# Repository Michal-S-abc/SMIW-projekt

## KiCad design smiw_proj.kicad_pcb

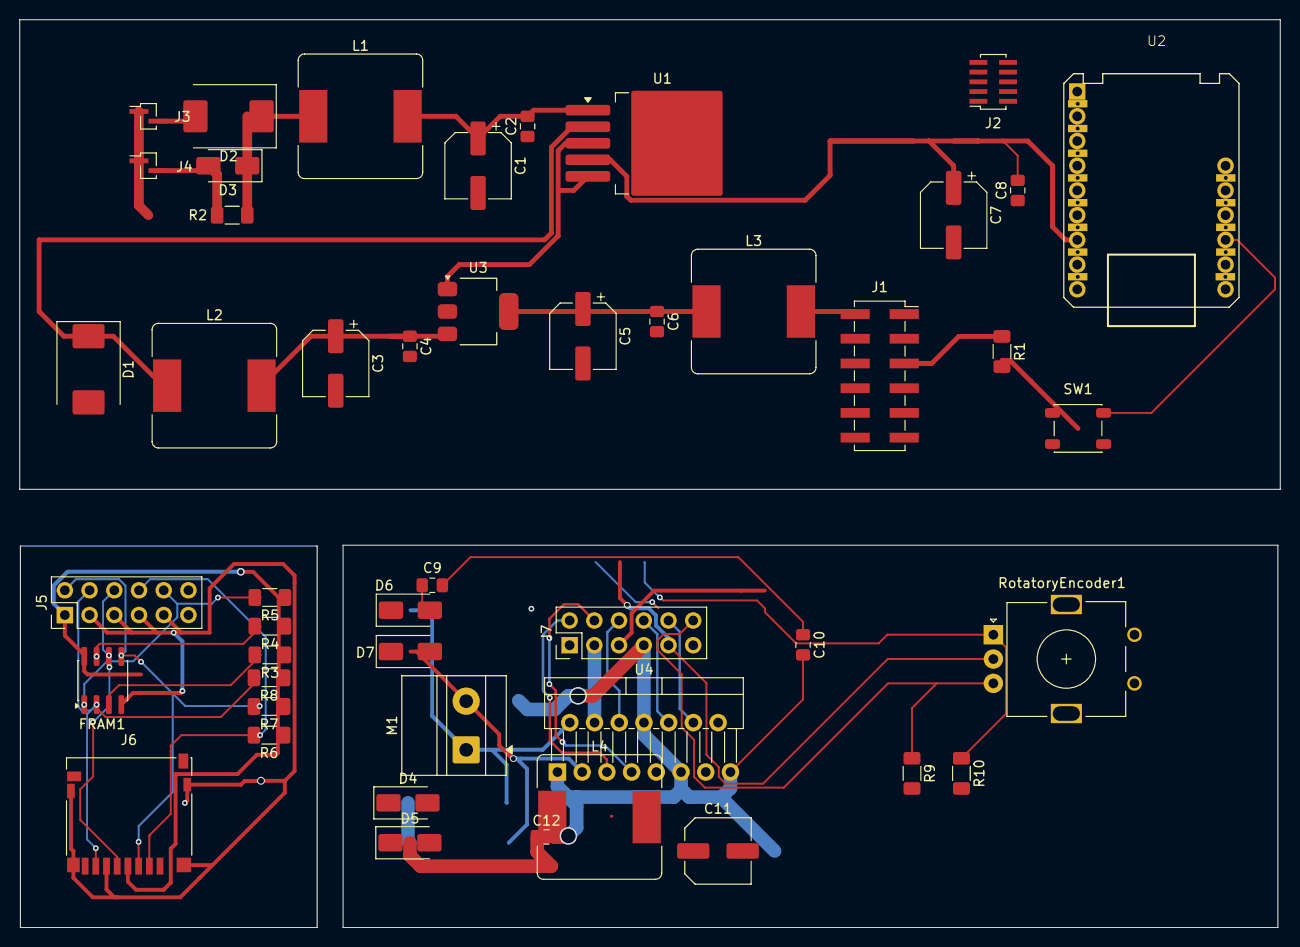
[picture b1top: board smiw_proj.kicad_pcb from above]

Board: 2 copper layers, 129.5 x 93.3 mm, 48 parts (0 on the bottom side), 31 nets.

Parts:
C1, C7: 100uF/16V; CP_Elec_6.3x5.3
C2, C6, C8, C9, C10, C12: 100nF; C_0805_2012Metric_Pad1.18x1.45mm_HandSolder
C3: 220uF/6V3; CP_Elec_6.3x5.3
C4: 220nF; C_0805_2012Metric_Pad1.18x1.45mm_HandSolder
C5: 10uF/16V; CP_Elec_6.3x5.3
C11: 100uF/16V; C_Elec_6.3x7.7
D1: 1N5824; D_SMC
D2: SS14; D_SMC
D3: SS14; D_SMA
D4, D5, D6, D7: 1N4001; D_SMA
FRAM1: CY15B104Q; SOIC-8_3.9x4.9mm_P1.27mm
J1: Conn_02x06_Odd_Even; PinSocket_2x06_P2.54mm_Vertical_SMD
J2: Conn_02x05_Odd_Even; PinSocket_2x05_P1.00mm_Vertical_SMD
J3, J4: Conn_01x02; PinSocket_1x02_P1.00mm_Vertical_SMD_Pin1Left
J5: Conn_02x05_Odd_Even; PinHeader_2x06_P2.54mm_Vertical
J6: Molex 104031; microSD_HC_Hirose_DM3D-SF
J7: Conn_02x06_Odd_Even; PinHeader_2x06_P2.54mm_Vertical
L1, L3: 10uH; L_Bourns_SRR1260
L2: 33uH; L_Bourns_SRR1260
L4: 1uH; L_Bourns_SRR1260
M1: JGB37-520; TerminalBlock_MetzConnect_Type011_RT05502HBLC_1x02_P5.00mm_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
R1, R3, R4, R5, R6, R7, R8: 10k; R_1206_3216Metric_Pad1.30x1.75mm_HandSolder
R2, R9, R10: 1k; R_1206_3216Metric_Pad1.30x1.75mm_HandSolder
RotatoryEncoder1: EC11E15204A3; RotaryEncoder_Alps_EC11E_Vertical_H20mm
SW1: SW_Push; SW_SPST_PTS647_Sx50
U1: LM2596S-5; TO-263-5_TabPin3
U2: M5 Stamp-S3; M5Stamp-S3
U3: LD1117S33TR_SOT223; SOT-223-3_TabPin2
U4: L298N; TO-220-15_P2.54x5.08mm_StaggerOdd_Lead4.58mm_Vertical

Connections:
12V: D2.1 (K), D3.1 (K), J1.1, J7.1, L1.1, L4.1, R2.1
/DRIVER IN1: J1.2, J7.2, U2.1 (g1), U4.5 (IN1)
/DRIVER IN2: J1.4, J7.4, U2.2 (g2), U4.7 (IN2)
/DRIVER IN3: J1.8, J7.8, U2.3 (g3), U4.10 (IN3)
/DRIVER IN4: J1.10, J7.10, U2.9 (g9), U4.12 (IN4)
/ENC A: J1.11, J7.11, R10.1, RotatoryEncoder1.A, U2.10 (g10)
/ENC B: J1.12, J7.12, R9.1, RotatoryEncoder1.B, U2.12 (g11)
/MISO: FRAM1.2 (SO), J2.4, J5.4, J6.7 (DAT0), R8.2, U2.4 (g4)
/MOSI: FRAM1.5 (SI), J2.2, J5.2, J6.3 (CMD), R7.2, U2.5 (g5)
/PWM A: J1.6, J7.6, U2.14 (g12), U4.6 (EnA)
/SCK: FRAM1.6 (SCK), J2.6, J5.6, J6.5 (CLK), U2.6 (g6)
/reset: R1.2, SW1.1, U2.22 (en)
//FRAM CS: FRAM1.1 (~CS), J5.10, R5.2
//SD CS: J5.8, J6.2 (DAT3/CD), R6.2
/~FRAM CS: J2.10, U2.8 (g8)
/~SD CS: J2.8, U2.7 (g7)
CPU_GND: J1.9, J7.9, RotatoryEncoder1.C
GND: C1.2, C2.1, C3.2, C4.2, C5.2, C6.2, C7.2, C8.1, C9.1, C10.2, C11.2, C12.2, D1.2 (A), D6.2 (A), D7.2 (A), FRAM1.4 (V_{SS}), J1.7, J2.3, J2.5, J2.7, J2.9, J3.1, J4.1, J5.3, J5.5, J5.7, J5.9, J6.6 (VSS), J6.SH (SHIELD), J7.7, SW1.2, U1.3 (GND), U1.5 (~ON/OFF), U2.11 (gnd), U2.18 (gnd), U3.1 (GND), U4.1 (SENSE_A), U4.8 (GND), U4.11 (EnB), U4.15 (SENSE_B)
unnamed: D1.1 (K), L2.1, U1.2 (OUT)
unnamed: D2.2 (A), J3.2
unnamed: D3.2 (A), J4.2, R2.2
unnamed: D4.2 (A), D6.1 (K), M1.1 (+), U4.2 (OUT1)
unnamed: C11.1, C12.1, D4.1 (K), D5.1 (K), L4.2, U4.9 (Vss)
unnamed: D5.2 (A), D7.1 (K), M1.2 (-), U4.3 (OUT2)
unnamed: FRAM1.7 (~HOLD), R4.2
unnamed: FRAM1.3 (~WP), R3.2
unnamed: C1.1, C2.2, L1.2, U1.1 (VIN)
unnamed: C5.1, C6.1, L3.1, U3.2 (VO)
VDD: C9.2, C10.1, FRAM1.8 (V_{CC}), J5.1, J6.4 (VDD), R3.1, R4.1, R5.1, R6.1, R7.1, R8.1
Vcc: C3.1, C4.1, C7.1, C8.2, J1.3, J7.3, L2.2, U1.4 (FB), U2.13 (5V), U3.3 (VI), U4.4 (Vs)
Vdd: J1.5, J2.1, J7.5, L3.2, R1.1, R9.2, R10.2

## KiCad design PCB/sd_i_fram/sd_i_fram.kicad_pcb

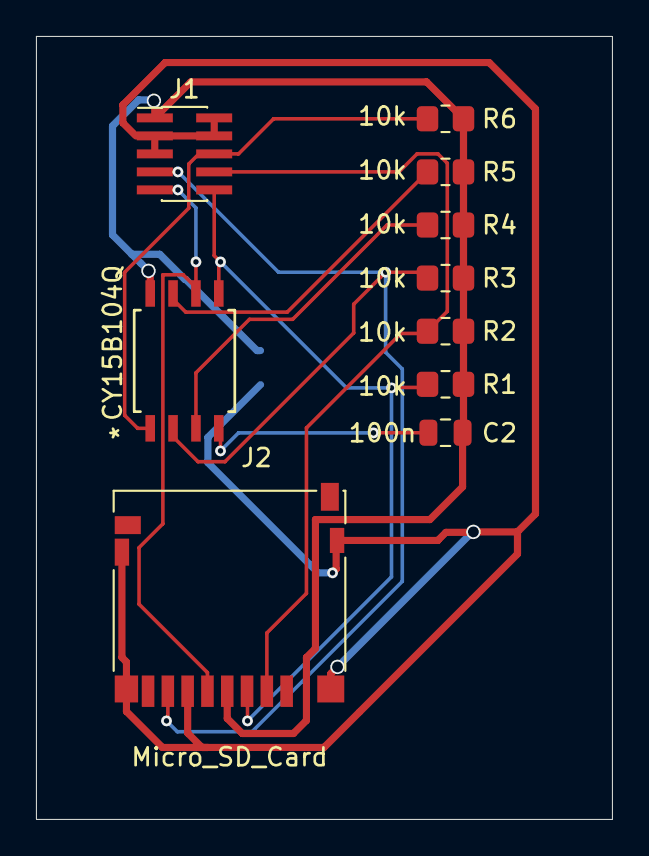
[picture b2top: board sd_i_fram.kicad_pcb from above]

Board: 2 copper layers, 32.0 x 43.5 mm, 11 parts (1 on the bottom side), 10 nets.

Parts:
C1, C2: 100n; C_0805_2012Metric
FRAM1: CY15B104Q; SOIC8_CY15B104Q-SXI_CYP
J1: Conn_02x05; PinHeader_2x05_P1.00mm_Vertical_SMD
J2: Micro_SD_Card; microSD_HC_Hirose_DM3D-SF
R1, R2, R3, R4, R5, R6: 10k; R_0805_2012Metric_Pad1.20x1.40mm_HandSolder

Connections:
/FRAM CS: FRAM1.1 (~CS), J1.6, R6.2
/GND_CPU: C1.2, J1.2, J1.3, J1.4, J1.5, J2.6 (VSS), J2.SH (SHIELD)
/MISO: FRAM1.2 (SO), J1.7, J2.7 (DAT0), R3.2
/MOSI: FRAM1.5 (SI), J1.10, J2.3 (CMD), R1.2
/SCK: FRAM1.6 (SCK), J1.9, J2.5 (CLK)
/SD CS: J1.8, J2.2 (DAT3/CD), R2.2
/VDD: C1.1, C2.2, FRAM1.8 (V_{CC}), J1.1, J2.4 (VDD), R1.1, R2.1, R3.1, R4.1, R5.1, R6.1
unnamed: C2.1, FRAM1.4 (V_{SS})
unnamed: FRAM1.7 (~HOLD), R5.2
unnamed: FRAM1.3 (~WP), R4.2

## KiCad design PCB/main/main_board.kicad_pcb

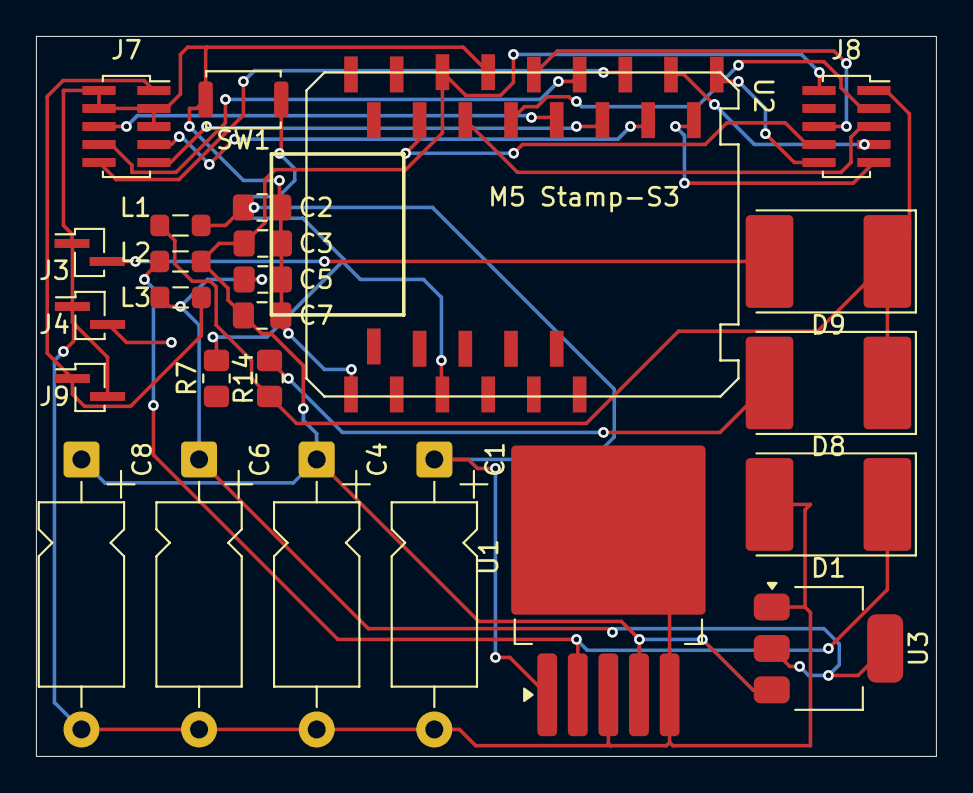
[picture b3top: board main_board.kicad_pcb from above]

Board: 4 copper layers, 50.0 x 40.0 mm, 25 parts (0 on the bottom side), 22 nets.

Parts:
C1, C8: 100u/16V1; CP_Axial_L10.0mm_D4.5mm_P15.00mm_Horizontal
C2, C7: 100n; C_0805_2012Metric_Pad1.18x1.45mm_HandSolder
C3: 220n; C_0805_2012Metric_Pad1.18x1.45mm_HandSolder
C4: 220u/6V3; CP_Axial_L10.0mm_D4.5mm_P15.00mm_Horizontal
C5: 100n2; C_0805_2012Metric_Pad1.18x1.45mm_HandSolder
C6: 10u/16V1; CP_Axial_L10.0mm_D4.5mm_P15.00mm_Horizontal
D1: 1N5824; D_3220_8050Metric_Pad2.65x5.15mm_HandSolder
D8, D9: D_Schottky; D_3220_8050Metric_Pad2.65x5.15mm_HandSolder
J3, J4, J9: Conn_01x02; PinSocket_1x02_P1.00mm_Vertical_SMD_Pin1Left
J7, J8: Conn_02x05; PinSocket_2x05_P1.00mm_Vertical_SMD
L1, L3: 10uH; L_0805_2012Metric_Pad1.05x1.20mm_HandSolder
L2: 33uH; L_0805_2012Metric_Pad1.05x1.20mm_HandSolder
R7: 10k; R_0805_2012Metric_Pad1.20x1.40mm_HandSolder
R14: 1k; R_0805_2012Metric_Pad1.20x1.40mm_HandSolder
SW1: SW_Push; SW_Push_SPST_NO_Alps_SKRK
U1: LM2596S-5; TO-263-5_TabPin3
U2: M5 Stamp-S3; Stamp-S3_PIN1.27_Socket
U3: LD1117S33TR_SOT223; SOT-223-3_TabPin2

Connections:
/5V: C3.1, C4.1, C7.2, C8.1, J8.2, L2.2, U1.4 (FB), U2.13 (5V), U3.3 (VI)
/12V: D8.1 (K), D9.1 (K), J8.1, L1.1, R14.1
/DRIVER IN1: J8.10, U2.1 (g1)
/DRIVER IN2: J8.9, U2.2 (g2)
/DRIVER IN3: J8.7, U2.3 (g3)
/DRIVER IN4: J8.6, U2.9 (g9)
/ENC A: J8.3, U2.10 (g10)
/ENC B: J8.5, U2.12 (g11)
/FRAM CS: J7.6, U2.8 (g8)
/MISO: J7.7, U2.4 (g4)
/MOSI: J7.10, U2.5 (g5)
/PWM A: J8.8, U2.14 (g12)
/SCK: J7.9, U2.6 (g6)
/SD CS: J7.8, U2.7 (g7)
GND: C1.2, C2.1, C3.2, C4.2, C5.2, C6.2, C7.1, C8.2, D1.2 (A), J3.1, J4.1, J7.2, J7.3, J7.4, J7.5, J9.2, SW1.2, U1.3 (GND), U1.5 (~ON/OFF), U2.11 (gnd), U2.18 (gnd), U3.1 (GND)
unnamed: D1.1 (K), L2.1, U1.2 (OUT)
unnamed: D8.2 (A), J4.2, R14.2
unnamed: D9.2 (A), J3.2
unnamed: C1.1, C2.2, L1.2, U1.1 (VIN)
unnamed: R7.2, SW1.1, U2.22 (en)
unnamed: C5.1, C6.1, L3.1, U3.2 (VO)
VDD: J7.1, J9.1, L3.2

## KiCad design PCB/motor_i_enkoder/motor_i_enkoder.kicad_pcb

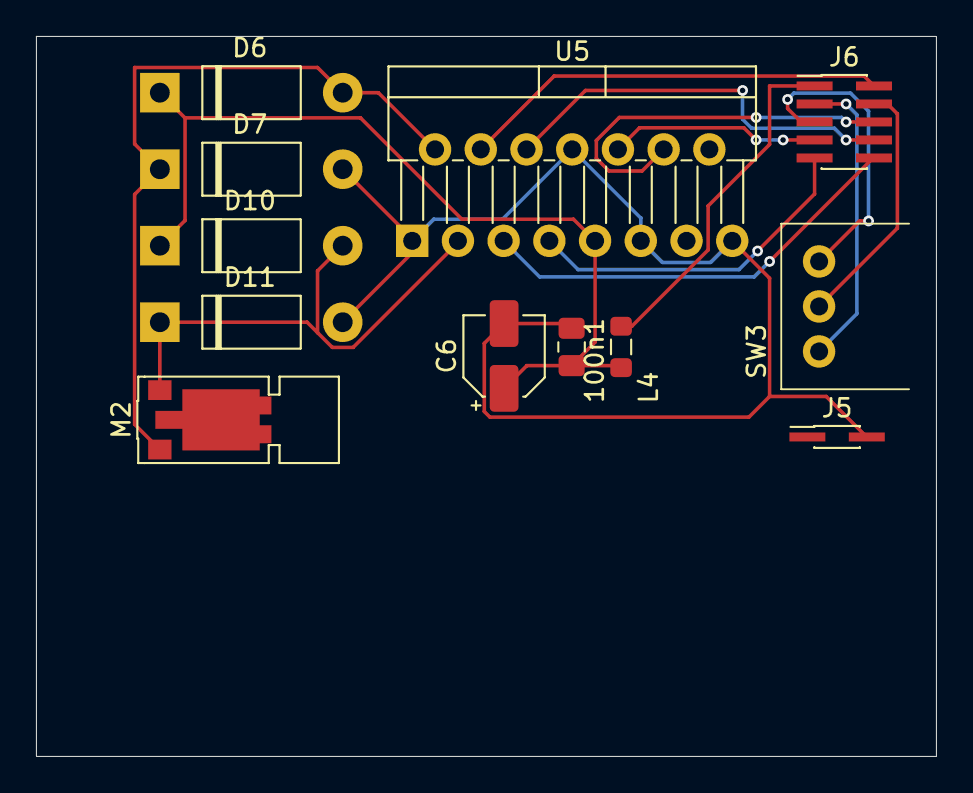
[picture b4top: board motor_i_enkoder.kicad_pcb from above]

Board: 2 copper layers, 50.0 x 40.0 mm, 12 parts (0 on the bottom side), 14 nets.

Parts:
100n1: C5; C_0805_2012Metric_Pad1.18x1.45mm_HandSolder
C6: 100u/16V2; CP_Elec_4x3
D6, D7, D10, D11: 1N4001; P1_DO-41
J5: Conn_01x02; PinHeader_2x01_P1.00mm_Vertical_SMD
J6: Conn_02x05; PinHeader_2x05_P1.00mm_Vertical_SMD
L4: 1uH; L_0805_2012Metric_Pad1.05x1.20mm_HandSolder
M2: Motor_DC; Vybronics_VZ30C1T8219732L
SW3: RotaryEncoder; RotaryEncoder_Bourns_Horizontal_PEC09-2xxxF-Nxxxx
U5: L298N; TO-220-15_P2.54x5.08mm_StaggerOdd_Lead4.58mm_Vertical

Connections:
/5V Z LM: J6.2, U5.4 (Vs)
/CPU_GND: J6.4, SW3.C
/DRIVER IN1: J6.10, U5.5 (IN1)
/DRIVER IN2: J6.9, U5.7 (IN2)
/DRIVER IN3: J6.7, U5.10 (IN3)
/DRIVER IN4: J6.6, U5.12 (IN4)
/ENC A: J6.3, SW3.A
/ENC B: J6.5, SW3.B
/PWM A: J6.8, U5.6 (EnA)
/ZASILANIE 12V: J6.1, L4.1
GND: 100n1.2, C6.2, D7.2 (A), D11.2 (A), J5.2, U5.1 (SENSE_A), U5.8 (GND), U5.11 (EnB), U5.15 (SENSE_B)
unnamed: D6.2 (A), D7.1 (K), M2.1 (+), U5.2 (OUT1)
unnamed: D10.2 (A), D11.1 (K), M2.2 (-), U5.3 (OUT2)
unnamed: 100n1.1, C6.1, D6.1 (K), D10.1 (K), L4.2, U5.9 (Vss)

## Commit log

2026-05-28 wersja "skonczona" 1
    wersja prawdopodobnie bez zadnych wiekszych bledow. Trzeba zrobic pcb, nazwac niektore elementy, sprawdzic czy polaczenia sa ok.
2026-05-28 pdf
    pdf do pogladu, zebyscie nie musieli pobierac do sprawdzenia
2026-05-30 pcb dodane!
2026-06-07 Add files via upload
    Jeszcze PCB
2026-06-07 poprawki po 'pracy' michala na schemacie. Poprawione PCB pamieci po Kubie. Grubsze sciezki, poprawiona pozycja decoupling capacitora
2026-06-09 dodane footprinty
2026-06-09 pcb prawie gotowe. czekam na werdykt o Vcc
2026-06-09 poprawka
2026-06-11 już prawie, jedno sprawdzenie
